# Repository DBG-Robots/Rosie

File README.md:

# Rosie

A small robot controller board for learning ROS and micro-ROS. It was designed by the DBG-Robots team at the Dietrich-Bonhoeffer-Gymnasium Oberasbach for students between 14 and 18.

**Status: v0.1, not built or tested yet.** The design passes KiCad's ERC and DRC and was checked against the datasheets, but no board has been powered up. The first batch is ordered from JLCPCB, and this README will get a "what we got wrong" section once the boards arrive. Treat everything below as the plan, not as proven.

## What it is for

We teach robotics to students who mostly have never touched a microcontroller, let alone ROS. The usual options are either a Raspberry Pi with a pile of loose modules and jumper wires, or a finished kit where you can't see how anything works.

Rosie sits in between. One board holds everything a small wheeled robot needs: the ESP32-S3, four motor outputs with encoder inputs, servo outputs, power handling, and a few connectors for sensors. The ESP32 talks to a computer running ROS 2 through micro-ROS, so students write robot code the way professionals do and never solder a motor driver.

Two decisions shaped the whole board:

1. **Nothing to wire for the standard case.** The motor connectors match the motor we use, so a student plugs in a cable and drives.
2. **Mistakes should be survivable.** A reversed battery, a stalled motor or a shorted servo cable should trip a protection instead of destroying the board, because the board will be handled by teenagers in a classroom.

## Features

- **ESP32-S3-WROOM-1-N8R2** module (8 MB flash, 2 MB PSRAM), USB-C for flashing, serial and power.
- **Four DC motor outputs** from two DRV8833 dual H-bridges. Each output has an encoder input (quadrature, ESP32 pulse counters).
- **Two servo headers** with their own current-limited supply.
- **Lidar/UART header** with 5 V, **Qwiic/I2C** socket plus an extra I2C pin header, and a **6-pin GPIO header** (J12, four free ESP32 pins named P1 to P4).
- **RGB LED** (WS2812-compatible) and a **buzzer** for status and "hello world" feedback.
- **Battery voltage measurement** so firmware can warn before the cells run flat.
- **EN and BOOT buttons**, and a **power switch**.
- **Debug LEDs and test pads** so students (and we) can see which rail or fault is the problem without a multimeter in hand.
- **Mounting holes on LEGO's 8 mm grid** (72 × 64 mm apart), so the board can be bolted to Technic frames.

## Power

Rosie runs from **four AA cells in a flat holder** fixed under the board (NiMH 1900 to 2500 mAh gives roughly three hours, alkaline cells also work). That is 4.0 to 6.4 V.

> **Rosie does not charge batteries.** There is no charger on the board. Charge NiMH cells in an external AA charger and only then put them in the holder. Do not connect anything other than 4 AA cells (max 6.4 V) to the battery connector. Do not put lithium cells there.

Why AA cells and not a LiPo: they are cheap, they can be bought in any shop, students swap them in seconds, and a classroom full of lithium cells and 14-year-olds is a risk we did not want. The price is that the voltage sags and that the board needs a good 3.3 V converter.

### Rails

| Rail | Comes from | Feeds |
|---|---|---|
| +BATT | AA holder, through a resettable fuse and a reverse-polarity P-FET | power switch |
| VSYS | after the power switch, 4.0 to 6.4 V | motors, servo supply, logic supply |
| VBUS | USB-C | logic supply only |
| VLOGIC | the higher of VSYS and VBUS (two Schottky diodes) | the 3.3 V converter |
| +3V3 | TPS62130A buck converter, 3.31 V | ESP32, pull-ups, buzzer, 5 V converter |
| +5V | TPS61023 boost converter from 3.3 V, 5.06 V | RGB LED, lidar header |
| VSERVO | TPS259571 eFuse, 2 A limit | servo headers |
| +3V3_EXT | SY6280 switch, 0.57 A limit | encoders, I2C, GPIO header |
| +5V_EXT | SY6280 switch, 0.68 A limit | lidar header |

The important consequences:

- **USB powers only the logic.** You can plug in USB to flash and debug without the motors or servos moving. Motors need the battery and the power switch.
- **USB never feeds the battery rails.** The two diodes stop current going the other way.
- **The 3.3 V converter runs from 3 to 17 V and can stay at 100 % duty**, so the ESP32 keeps running while the cells droop towards 4 V. A linear regulator would have lost the 3.3 V earlier and wasted battery as heat.
- **Servos get their own protected rail.** A shorted servo cable current-limits and shuts down that rail only. The ESP32 keeps running and the red SRV ERR LED turns on if it overheats.
- **Encoders and sensors are supplied by switches with a current limit** (SY6280), so a shorted sensor cable does not take the 3.3 V rail down with it.

## Connectors

All pinouts are listed from pin 1.

| Ref | Connector | Pins |
|---|---|---|
| J1 | USB-C | power, flashing, serial console |
| J2 | JST XH, 2-pin | battery: pin 1 = +, pin 2 = GND |
| J3 to J6 | JST ZH 1.5 mm, 6-pin | motors M1 to M4: 1 motor-, 2 GND, 3 encoder A, 4 encoder B, 5 +3.3 V, 6 motor+ |
| J7 | JST SH, 4-pin | Qwiic: GND, 3.3 V, SDA, SCL |
| J8 | 2.54 mm header, 4-pin | I2C: GND, 3.3 V, SDA, SCL |
| J9, J10 | 2.54 mm header, 3-pin | servo 1 and 2: GND, servo supply, signal |
| J11 | 2.54 mm header, 4-pin | lidar UART: GND, 5 V, RX, TX |
| J12 | 2.54 mm header, 6-pin | GND, 3.3 V, P1, P2, P3, P4 |

The motors are numbered counter-clockwise looking from above: M1 front-left, M2 rear-left, M3 rear-right, M4 front-right.

The motor connector order is that of the **CHIHAI CHF-GM12-N20** gear motor with its 6-pin ZH cable (6 V, hall encoder). Other N20 motors use other pin orders, and a wrong order can swap encoder power and ground. Plug a new motor type in with the board unpowered and check with a multimeter first.

Every encoder, servo, UART and GPIO signal passes through a 1 kΩ series resistor. A wrong connection then pushes only a milliamp or two into the ESP32 pin instead of burning it.

## Debug LEDs and test pads

| LED | Silk | Lights when |
|---|---|---|
| green | 3V3 | the 3.3 V rail is up |
| green | USB | USB power is present |
| green | BAT ON | the power switch is on and the battery is connected |
| yellow | MOT ON | firmware has enabled the motor drivers |
| red | MOT ERR | a DRV8833 reports overcurrent, overheating or undervoltage |
| red | SRV ERR | the servo eFuse shut down because of overheating |

If a rail is in doubt, the 1.5 mm round **test pads** on the top side give direct access to BAT, VSYS, VBUS, VLOG, 3V3, 5V, 3V3X, 5VX, VSRV, EN, BOOT, MOT_EN, MOT_FLT, VBAT and three ground points. Hold a multimeter probe on the pad and a second one on GND.

The four expansion pins on J12 are labelled P1 to P4 on the board on purpose. We did not want ESP32 GPIO numbers printed on the silk, because students would start thinking in pin numbers instead of functions. A student guide will map P1 to P4 to GPIOs.

## GPIO map

| GPIO | Function |
|---|---|
| IO6, IO7 | M1 PWM inputs |
| IO16, IO15 | M2 PWM inputs |
| IO37, IO38 | M3 PWM inputs |
| IO40, IO39 | M4 PWM inputs |
| IO5, IO4 | encoder 1 A, B |
| IO17, IO18 | encoder 2 A, B |
| IO36, IO35 | encoder 3 A, B |
| IO41, IO42 | encoder 4 A, B |
| IO10 | motor driver enable (internal pull-down, so motors stay off while the ESP32 boots) |
| IO21 | motor driver fault input (both drivers wired together) |
| IO8, IO9 | I2C SDA, SCL |
| IO11, IO12 | servo 1 and 2 PWM |
| IO43, IO44 | UART0 TX, RX (lidar header) |
| IO47 | buzzer |
| IO48 | RGB LED data |
| IO1, IO2, IO13, IO14 | J12 pins P1 to P4 (P1 and P2 can read analog) |
| IO3 | battery voltage (divider 1:3, so 6.4 V reads as 2.13 V) |
| IO0, IO19, IO20 | BOOT, USB D-, USB D+ |
| IO45, IO46 | strapping pins, not connected |

The firmware should **ramp the motors up** instead of jumping to full power. Four stalled N20 motors can briefly pull more than the AA cells can give, and the resulting voltage dip can reset the ESP32. Warn at 4.4 V battery voltage and stop the motors at 4.0 V.

## Design decisions

### Parts and cost

The board is built for **JLCPCB Economic assembly**, which means single-sided SMD assembly, and a limited parts catalogue. Every part was checked for stock and Economic eligibility. JLC charges $3.07 for each *unique* "Extended" part per order and nothing extra for "Basic" parts, so we:

- chose Basic parts wherever one exists (all the resistors except the 0.2 Ω shunts, all capacitors, diodes, MOSFETs, LEDs, buttons),
- recalculated the voltage dividers to values that exist as Basic resistors (3.3 V: 47 k / 15 k, 5 V: 15 k / 2 k),
- accepted 14 Extended parts, because there is no Basic alternative for the ICs, USB-C connector, ZH connector, inductor, fuse, buzzer and RGB LED.

The first order of five assembled boards came to roughly $112 before shipping and VAT, which is about $22 per board. More boards per order is the cheapest way to lower that, since the Extended-part fee is fixed.

The ESP32 module, the pin headers, the XH battery connector and the slide switch are **hand-soldered**. The JST ZH motor connectors are through-hole too, but JLC solders them. The full list with LCSC numbers is in [PARTS.md](PARTS.md), including the checks against the datasheets.

### Board and layout

- 80 × 72 mm, **four layers**: top = parts and power, inner 1 = unbroken ground, inner 2 = 3.3 V plane with a few thin power traces, bottom = signals. We chose four layers because the DRV8833s and the buck converter need a quiet ground, and because the cost difference at this size is small.
- All SMD parts are on the top side, because Economic assembly does single-sided only.
- The bottom side is flat enough that a 4×AA holder can be taped or screwed under the board. No through-hole parts sit in the 62 × 58 mm area in the middle of the bottom. Where the holder goes is up to the student; the board has no holder holes.
- The four M3 mounting holes are 72 × 64 mm apart, which is 9 × 8 studs on LEGO's 8 mm grid. Bolt them to Technic beams or use standoffs. The solder tails and the AA holder need 5 to 8 mm of room below.
- Signals were routed by hand by the team. The autorouter was tried and dropped.

### Motor drivers

The DRV8833 is a cheap, well-known dual H-bridge, with a current limit set by resistors. We use the two-pin PWM mode, and all four outputs share one enable and one fault line. Four motors on two chips keep the part count low.

### Protection

- A P-FET (not a diode) handles reverse battery polarity, so there is almost no voltage drop.
- A 3 A resettable fuse sits after the battery connector. Be aware that this kind of fuse trips at lower current when warm (about 2.3 A at 50 °C), so a warm robot can trip it at stall currents a cold one handles.
- USB data lines have an ESD protection chip.
- Servo and sensor rails have current limiting as described above.

### Silkscreen

JLCPCB wants silkscreen text at least 1.0 mm tall with a 0.15 mm stroke, so all labels are at that size or larger. The slide switch has no ON/OFF labels yet, because we have not verified which direction is ON on the real part.

The QR code at the top right links to our GitHub organization. It is drawn as silkscreen so that the code area is mask-coloured on a white silk background, which scans like a printed code.

## Files

| Path | What |
|---|---|
| `Rosie.kicad_pro`, `.kicad_sch`, `.kicad_pcb` | KiCad 10 project. Sheets: MCU, power input, power conversion, motor drivers, I/O peripherals, USB, debug |
| `libs/` | project symbols, footprints and 3D models for the parts that KiCad's own libraries do not have |
| `libs/3d-generator/` | script that generates the simplified 3D models (needs FreeCAD) |
| `production/` | Gerbers (`Rosie.zip`), JLC BOM and position files |
| `PARTS.md` | part numbers, datasheet checks, rail and GPIO tables |
| `docs/` | pictures |

Open `Rosie.kicad_pro` in KiCad 10. The library tables use relative paths, so it should work wherever you clone it.

## Known open points

- The ON direction of the slide switch SW3 is unverified (hence no labels).
- No hardware test yet. First checks when boards arrive: all red LEDs dark with only USB connected, 3.3 V and 5 V rails measured, 5 V rail noise after the divider change, LED brightness.
- 3D models are simplified and drawn from datasheet outlines, not from the manufacturers' CAD.
- Silkscreen: four footprint outlines (USB-C and the ESP32 footprint) reach past the board edge. This is harmless.

## Licence

Hardware design files (schematics, PCB, footprints, models, production files): **CERN-OHL-S-2.0**, see [LICENSE-hardware.txt](LICENSE-hardware.txt). In short: you may build, modify and sell it, but if you share a modified design, it has to stay open under the same licence. Firmware and software live in separate repositories with their own licences.

## Credits

Designed by Merlin Ortner with the DBG-Robots team, Dietrich-Bonhoeffer-Gymnasium Oberasbach.

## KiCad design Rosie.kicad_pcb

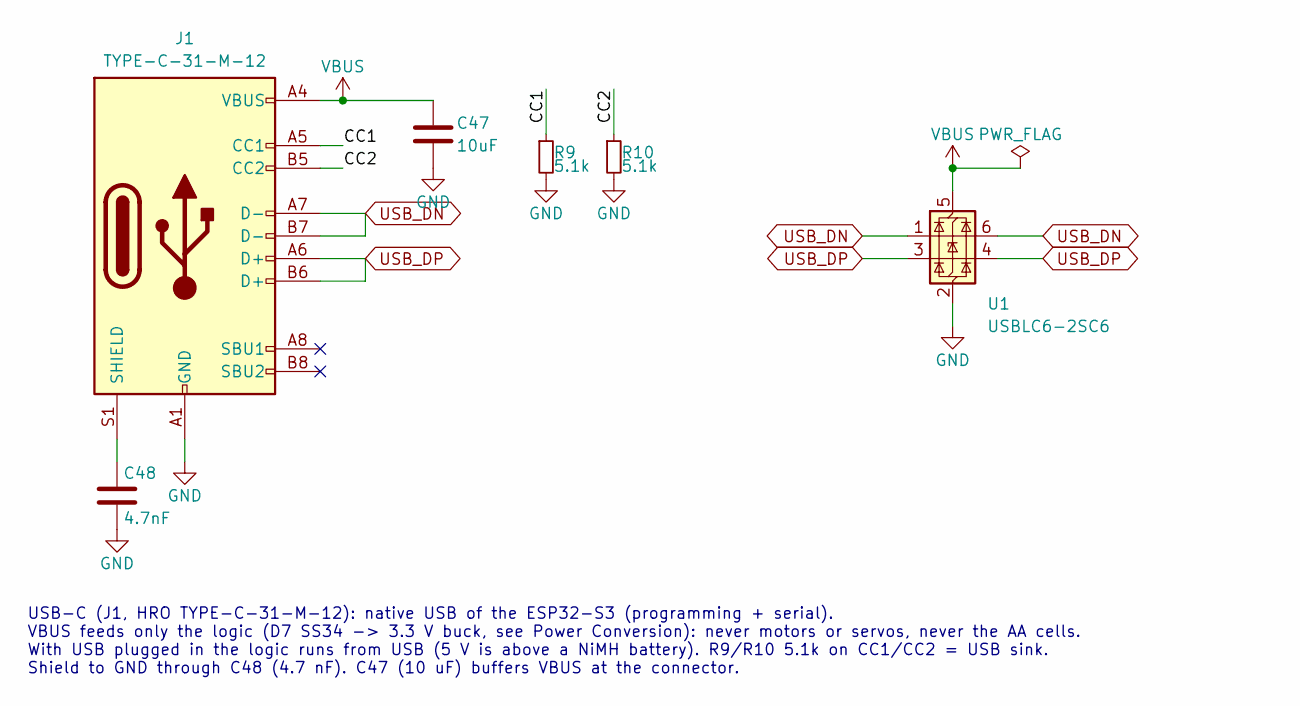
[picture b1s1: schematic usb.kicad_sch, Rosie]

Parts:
C47: 10uF; C_0805_2012Metric
C48: 4.7nF; C_0402_1005Metric
J1: TYPE-C-31-M-12; USB_C_Receptacle_HRO_TYPE-C-31-M-12; LCSC Part C165948
R9, R10: 5.1k; R_0402_1005Metric
U1: USBLC6-2SC6; SOT-23-6; LCSC Part C7519

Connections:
/USB/CC1: J1.A5 (CC1), R9.1
/USB/CC2: J1.B5 (CC2), R10.1
GND: C47.2, C48.2, J1.A1 (GND), J1.A12 (GND), J1.B1 (GND), J1.B12 (GND), R9.2, R10.2, U1.2 (GND); also elsewhere on the board
unnamed: C48.1, J1.S1 (SHIELD)
USB_DN: J1.A7 (D-), J1.B7 (D-), U1.1 (I/O1), U1.6 (I/O1); also elsewhere on the board
USB_DP: J1.A6 (D+), J1.B6 (D+), U1.3 (I/O2), U1.4 (I/O2); also elsewhere on the board
VBUS: C47.1, J1.A4 (VBUS), J1.A9 (VBUS), J1.B4 (VBUS), J1.B9 (VBUS), U1.5 (VBUS); also elsewhere on the board

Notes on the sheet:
USB-C (J1, HRO TYPE-C-31-M-12): native USB of the ESP32-S3 (programming + serial). VBUS feeds only the logic (D7 SS34 -> 3.3 V buck, see Power Conversion): never motors or servos, never the AA cells. With USB plugged in the logic runs from USB (5 V is above a NiMH battery). R9/R10 5.1k on CC1/CC2 =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

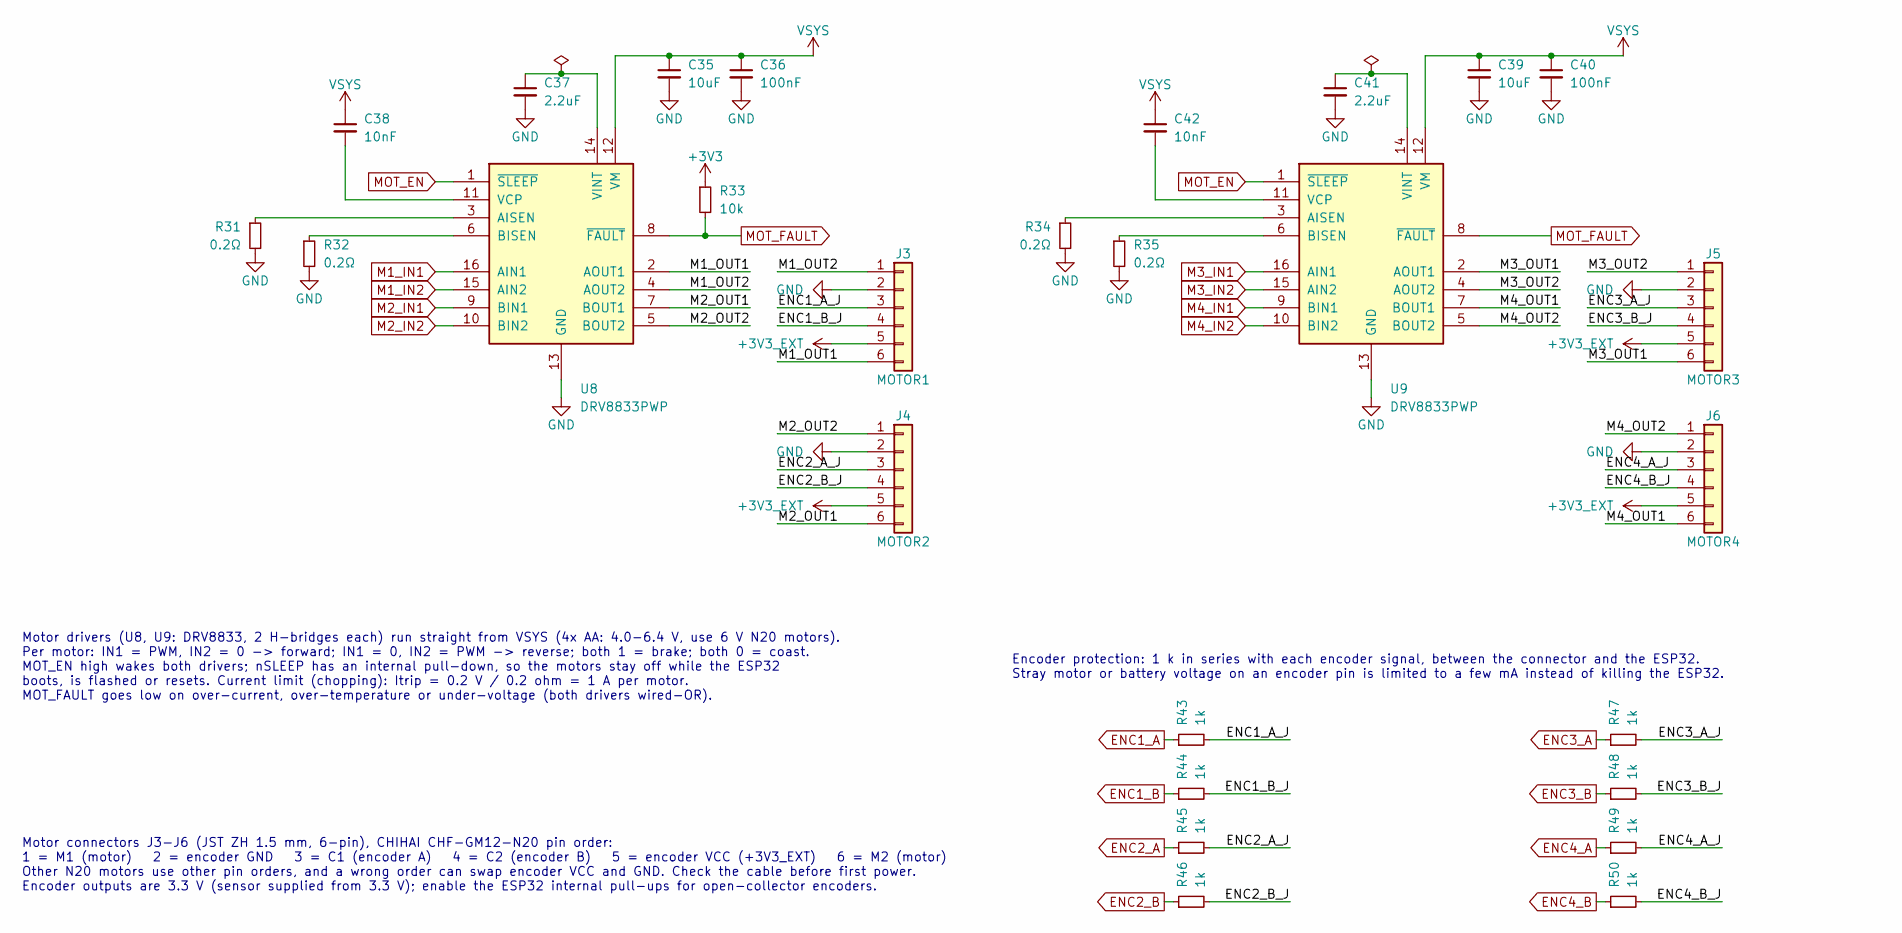
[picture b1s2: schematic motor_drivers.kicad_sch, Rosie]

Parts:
C35, C39: 10uF; C_0805_2012Metric
C36, C40: 100nF; C_0402_1005Metric
C37, C41: 2.2uF; C_0402_1005Metric
C38, C42: 10nF; C_0402_1005Metric
J3: MOTOR1; JST_ZH_B6B-ZR_1x06_P1.50mm_Vertical; LCSC Part C157984
J4: MOTOR2; JST_ZH_B6B-ZR_1x06_P1.50mm_Vertical; LCSC Part C157984
J5: MOTOR3; JST_ZH_B6B-ZR_1x06_P1.50mm_Vertical; LCSC Part C157984
J6: MOTOR4; JST_ZH_B6B-ZR_1x06_P1.50mm_Vertical; LCSC Part C157984
R31, R32, R34, R35: 0.2Ω; R_1206_3216Metric
R33: 10k; R_0402_1005Metric
R43, R44, R45, R46, R47, R48, R49, R50: 1k; R_0402_1005Metric
U8, U9: DRV8833PWP; HTSSOP-16-1EP_4.4x5mm_P0.65mm_EP3.4x5mm_ThermalVias_D0.3; LCSC Part C50506

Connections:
+3V3: R33.1; also elsewhere on the board
+3V3_EXT: J3.5, J4.5, J5.5, J6.5; also elsewhere on the board
/Motor Drivers/ENC1_A_J: J3.3, R43.2
/Motor Drivers/ENC1_B_J: J3.4, R44.2
/Motor Drivers/ENC2_A_J: J4.3, R45.2
/Motor Drivers/ENC2_B_J: J4.4, R46.2
/Motor Drivers/ENC3_A_J: J5.3, R47.2
/Motor Drivers/ENC3_B_J: J5.4, R48.2
/Motor Drivers/ENC4_A_J: J6.3, R49.2
/Motor Drivers/ENC4_B_J: J6.4, R50.2
/Motor Drivers/M1_OUT1: J3.6, U8.2 (AOUT1)
/Motor Drivers/M1_OUT2: J3.1, U8.4 (AOUT2)
/Motor Drivers/M2_OUT1: J4.6, U8.7 (BOUT1)
/Motor Drivers/M2_OUT2: J4.1, U8.5 (BOUT2)
/Motor Drivers/M3_OUT1: J5.6, U9.2 (AOUT1)
/Motor Drivers/M3_OUT2: J5.1, U9.4 (AOUT2)
/Motor Drivers/M4_OUT1: J6.6, U9.7 (BOUT1)
/Motor Drivers/M4_OUT2: J6.1, U9.5 (BOUT2)
ENC1_A: R43.1; also elsewhere on the board
ENC1_B: R44.1; also elsewhere on the board
ENC2_A: R45.1; also elsewhere on the board
ENC2_B: R46.1; also elsewhere on the board
ENC3_A: R47.1; also elsewhere on the board
ENC3_B: R48.1; also elsewhere on the board
ENC4_A: R49.1; also elsewhere on the board
ENC4_B: R50.1; also elsewhere on the board
GND: C35.2, C36.2, C37.2, C39.2, C40.2, C41.2, J3.2, J4.2, J5.2, J6.2, R31.2, R32.2, R34.2, R35.2, U8.13 (GND), U8.17 (GND), U9.13 (GND), U9.17 (GND); also elsewhere on the board
M1_IN1: U8.16 (AIN1); also elsewhere on the board
M1_IN2: U8.15 (AIN2); also elsewhere on the board
M2_IN1: U8.9 (BIN1); also elsewhere on the board
M2_IN2: U8.10 (BIN2); also elsewhere on the board
M3_IN1: U9.16 (AIN1); also elsewhere on the board
M3_IN2: U9.15 (AIN2); also elsewhere on the board
M4_IN1: U9.9 (BIN1); also elsewhere on the board
M4_IN2: U9.10 (BIN2); also elsewhere on the board
MOT_EN: U8.1 (~SLEEP), U9.1 (~SLEEP); also elsewhere on the board
MOT_FAULT: R33.2, U8.8 (~FAULT), U9.8 (~FAULT); also elsewhere on the board
unnamed: R31.1, U8.3 (AISEN)
unnamed: R32.1, U8.6 (BISEN)
unnamed: C38.2, U8.11 (VCP)
unnamed: C37.1, U8.14 (VINT)
unnamed: R34.1, U9.3 (AISEN)
unnamed: R35.1, U9.6 (BISEN)
unnamed: C42.2, U9.11 (VCP)
unnamed: C41.1, U9.14 (VINT)
VSYS: C35.1, C36.1, C38.1, C39.1, C40.1, C42.1, U8.12 (VM), U9.12 (VM); also elsewhere on the board

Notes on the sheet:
Encoder protection: 1 k in series with each encoder signal, between the connector and the ESP32. Stray motor or battery voltage on an encoder pin is limited to a few mA instead of killing the ESP32.
Motor connectors J3-J6 (JST ZH 1.5 mm, 6-pin), CHIHAI CHF-GM12-N20 pin order: 1 = M1 (motor) 2 = encoder GND 3 = C1 (encoder A) 4 = C2 (encoder B) 5 = encoder VCC (+3V3_EXT) 6 = M2 (motor) Other N20 motors use other pin orders, and a wrong order can swap encoder VCC and GND. Check the cable before 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
Motor drivers (U8, U9: DRV8833, 2 H-bridges each) run straight from VSYS (4x AA: 4.0-6.4 V, use 6 V N20 motors). Per motor: IN1 = PWM, IN2 = 0 -> forward; IN1 = 0, IN2 = PWM -> reverse; both 1 = brake; both 0 = coast. MOT_EN high wakes both drivers; nSLEEP has an internal pull-down, so the motors s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

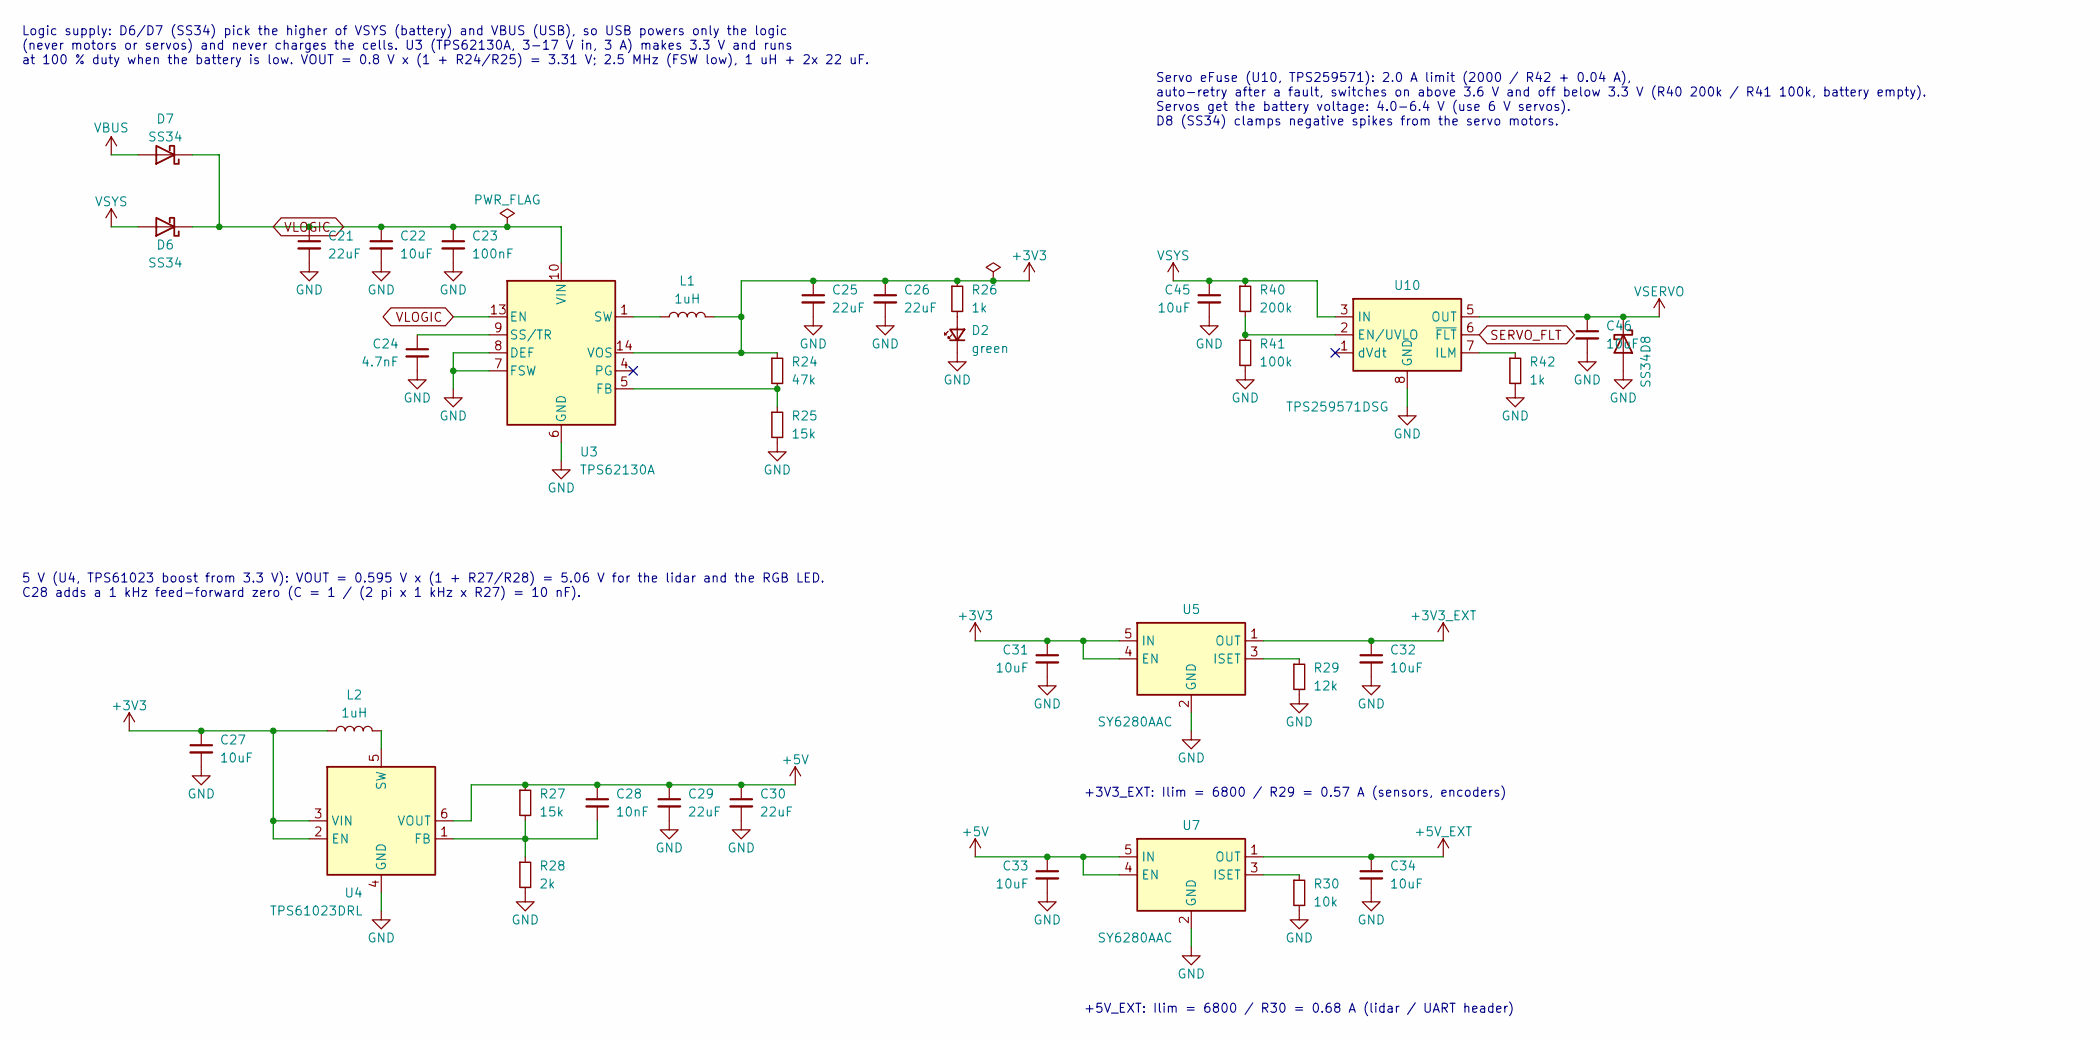
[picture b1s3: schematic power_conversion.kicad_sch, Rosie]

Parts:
C21, C25, C26, C29, C30: 22uF; C_0805_2012Metric
C22, C27, C31, C32, C33, C34, C45, C46: 10uF; C_0805_2012Metric
C23: 100nF; C_0402_1005Metric
C24: 4.7nF; C_0402_1005Metric
C28: 10nF; C_0402_1005Metric
D2: green; LED_0805_2012Metric; LCSC Part C2297
D6, D7, D8: SS34; D_SMA; LCSC Part C8678
L1, L2: 1uH; L_Changjiang_FNR4030S; LCSC Part C167865
R24: 47k; R_0402_1005Metric
R25, R27: 15k; R_0402_1005Metric
R26, R42: 1k; R_0402_1005Metric
R28: 2k; R_0402_1005Metric
R29: 12k; R_0402_1005Metric
R30: 10k; R_0402_1005Metric
R40: 200k; R_0402_1005Metric
R41: 100k; R_0402_1005Metric
U3: TPS62130A; VQFN-16-1EP_3x3mm_P0.5mm_EP1.68x1.68mm_ThermalVias_D0.3; LCSC Part C337502
U4: TPS61023DRL; SOT-563_TI_DRL; LCSC Part C919459
U5, U7: SY6280AAC; SOT-23-5; LCSC Part C55136
U10: TPS259571DSG; WSON-8-1EP_2x2mm_P0.5mm_EP0.9x1.6mm; LCSC Part C471038

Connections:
+3V3: C25.1, C26.1, C27.1, C31.1, L1.2, L2.1, R24.1, R26.1, U3.14 (VOS), U4.2 (EN), U4.3 (VIN), U5.4 (EN), U5.5 (IN); also elsewhere on the board
+3V3_EXT: C32.1, U5.1 (OUT); also elsewhere on the board
+5V: C28.1, C29.1, C30.1, C33.1, R27.1, U4.6 (VOUT), U7.4 (EN), U7.5 (IN); also elsewhere on the board
+5V_EXT: C34.1, U7.1 (OUT); also elsewhere on the board
GND: C21.2, C22.2, C23.2, C24.2, C25.2, C26.2, C27.2, C29.2, C30.2, C31.2, C32.2, C33.2, C34.2, C45.2, C46.2, D2.1 (K), D8.2 (A), R25.2, R28.2, R29.2, R30.2, R41.2, R42.2, U3.6 (GND), U3.7 (FSW), U3.8 (DEF), U3.15 (GND), U3.16 (GND), U3.17 (GND), U4.4 (GND), U5.2 (GND), U7.2 (GND), U10.8 (GND), U10.9 (GND); also elsewhere on the board
unnamed: D2.2 (A), R26.2
unnamed: L1.1, U3.1 (SW), U3.2 (SW), U3.3 (SW)
unnamed: R24.2, R25.1, U3.5 (FB)
unnamed: C24.1, U3.9 (SS/TR)
unnamed: C28.2, R27.2, R28.1, U4.1 (FB)
unnamed: L2.2, U4.5 (SW)
unnamed: R29.1, U5.3 (ISET)
unnamed: R30.1, U7.3 (ISET)
unnamed: R40.2, R41.1, U10.2 (EN/UVLO)
unnamed: R42.1, U10.7 (ILM)
SERVO_FLT: U10.6 (~FLT); also elsewhere on the board
VBUS: D7.2 (A); also elsewhere on the board
VLOGIC: C21.1, C22.1, C23.1, D6.1 (K), D7.1 (K), U3.10 (VIN), U3.11 (VIN), U3.12 (VIN), U3.13 (EN); also elsewhere on the board
VSERVO: C46.1, D8.1 (K), U10.5 (OUT); also elsewhere on the board
VSYS: C45.1, D6.2 (A), R40.1, U10.3 (IN), U10.4 (IN); also elsewhere on the board

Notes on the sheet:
5 V (U4, TPS61023 boost from 3.3 V): VOUT = 0.595 V x (1 + R27/R28) = 5.06 V for the lidar and the RGB LED. C28 adds a 1 kHz feed-forward zero (C = 1 / (2 pi x 1 kHz x R27) = 10 nF).
Logic supply: D6/D7 (SS34) pick the higher of VSYS (battery) and VBUS (USB), so USB powers only the logic (never motors or servos) and never charges the cells. U3 (TPS62130A, 3-17 V in, 3 A) makes 3.3 V and runs at 100 % duty when the battery is low. VOUT = 0.8 V x (1 + R24/R25) = 3.31 V; 2.5 MHz (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
Servo eFuse (U10, TPS259571): 2.0 A limit (2000 / R42 + 0.04 A), auto-retry after a fault, switches on above 3.6 V and off below 3.3 V (R40 200k / R41 100k, battery empty). Servos get the battery voltage: 4.0-6.4 V (use 6 V servos). D8 (SS34) clamps negative spikes from the servo motors.
+3V3_EXT: Ilim = 6800 / R29 = 0.57 A (sensors, encoders)
+5V_EXT: Ilim = 6800 / R30 = 0.68 A (lidar / UART header)

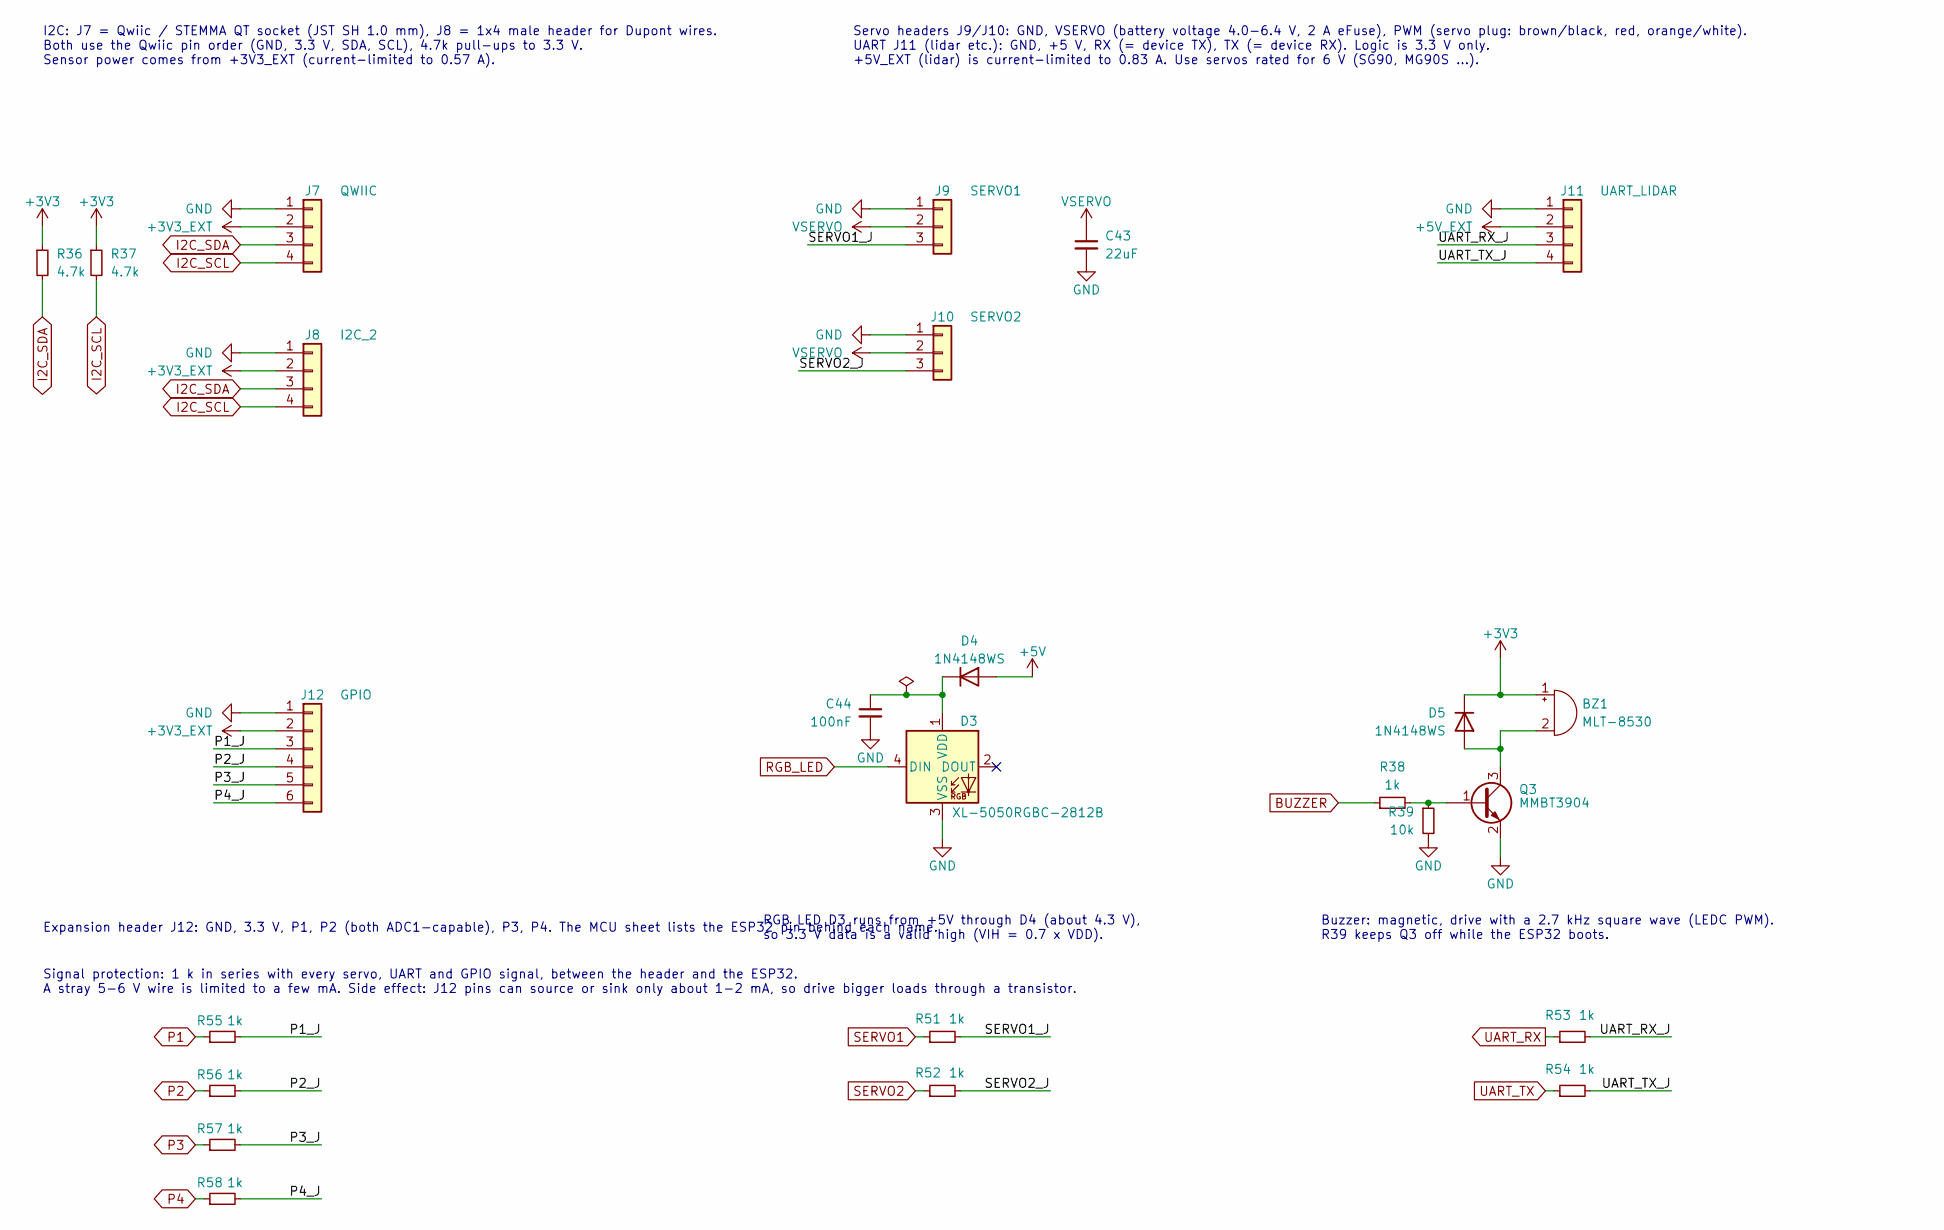
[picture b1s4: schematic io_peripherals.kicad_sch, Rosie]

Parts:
BZ1: MLT-8530; Buzzer_Huaneng_MLT-8530; LCSC Part C94599
C43: 22uF; C_0805_2012Metric
C44: 100nF; C_0402_1005Metric
D3: XL-5050RGBC-2812B; LED_WS2812B_PLCC4_5.0x5.0mm_P3.2mm; LCSC Part C48586674
D4, D5: 1N4148WS; D_SOD-323; LCSC Part C2128
J7: QWIIC; JST_SH_SM04B-SRSS-TB_1x04-1MP_P1.00mm_Horizontal; LCSC Part C160404
J8: I2C_2; PinHeader_1x04_P2.54mm_Vertical; LCSC Part C42431788 (cut to length)
J9: SERVO1; PinHeader_1x03_P2.54mm_Vertical; LCSC Part C42431788 (cut to length)
J10: SERVO2; PinHeader_1x03_P2.54mm_Vertical; LCSC Part C42431788 (cut to length)
J11: UART_LIDAR; PinHeader_1x04_P2.54mm_Vertical; LCSC Part C42431788 (cut to length)
J12: GPIO; PinHeader_1x06_P2.54mm_Vertical; LCSC Part C42431788 (cut to length)
Q3: MMBT3904; SOT-23; LCSC Part C20526
R36, R37: 4.7k; R_0402_1005Metric
R38, R51, R52, R53, R54, R55, R56, R57, R58: 1k; R_0402_1005Metric
R39: 10k; R_0402_1005Metric

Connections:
+3V3: BZ1.1 (+), D5.1 (K), R36.1, R37.1; also elsewhere on the board
+3V3_EXT: J7.2, J8.2, J12.2; also elsewhere on the board
+5V: D4.2 (A); also elsewhere on the board
+5V_EXT: J11.2; also elsewhere on the board
/IO Peripherals/P1_J: J12.3, R55.2
/IO Peripherals/P2_J: J12.4, R56.2
/IO Peripherals/P3_J: J12.5, R57.2
/IO Peripherals/P4_J: J12.6, R58.2
/IO Peripherals/SERVO1_J: J9.3, R51.2
/IO Peripherals/SERVO2_J: J10.3, R52.2
/IO Peripherals/UART_RX_J: J11.3, R53.2
/IO Peripherals/UART_TX_J: J11.4, R54.2
BUZZER: R38.1; also elsewhere on the board
GND: C43.2, C44.2, D3.3 (VSS), J7.1, J8.1, J9.1, J10.1, J11.1, J12.1, Q3.2 (E), R39.2; also elsewhere on the board
I2C_SCL: J7.4, J8.4, R37.2; also elsewhere on the board
I2C_SDA: J7.3, J8.3, R36.2; also elsewhere on the board
unnamed: BZ1.2 (-), D5.2 (A), Q3.3 (C)
unnamed: C44.1, D3.1 (VDD), D4.1 (K)
unnamed: Q3.1 (B), R38.2, R39.1
P1: R55.1; also elsewhere on the board
P2: R56.1; also elsewhere on the board
P3: R57.1; also elsewhere on the board
P4: R58.1; also elsewhere on the board
RGB_LED: D3.4 (DIN); also elsewhere on the board
SERVO1: R51.1; also elsewhere on the board
SERVO2: R52.1; also elsewhere on the board
UART_RX: R53.1; also elsewhere on the board
UART_TX: R54.1; also elsewhere on the board
VSERVO: C43.1, J9.2, J10.2; also elsewhere on the board

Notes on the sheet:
Buzzer: magnetic, drive with a 2.7 kHz square wave (LEDC PWM). R39 keeps Q3 off while the ESP32 boots.
Servo headers J9/J10: GND, VSERVO (battery voltage 4.0-6.4 V, 2 A eFuse), PWM (servo plug: brown/black, red, orange/white). UART J11 (lidar etc.): GND, +5 V, RX (= device TX), TX (= device RX). Logic is 3.3 V only. +5V_EXT (lidar) is current-limited to 0.83 A. Use servos rated for 6 V (SG90, MG90S 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
Signal protection: 1 k in series with every servo, UART and GPIO signal, between the header and the ESP32. A stray 5-6 V wire is limited to a few mA. Side effect: J12 pins can source or sink only about 1-2 mA, so drive bigger loads through a transistor.
I2C: J7 = Qwiic / STEMMA QT socket (JST SH 1.0 mm), J8 = 1x4 male header for Dupont wires. Both use the Qwiic pin order (GND, 3.3 V, SDA, SCL), 4.7k pull-ups to 3.3 V. Sensor power comes from +3V3_EXT (current-limited to 0.57 A).
RGB LED D3 runs from +5V through D4 (about 4.3 V), so 3.3 V data is a valid high (VIH = 0.7 x VDD).
Expansion header J12: GND, 3.3 V, P1, P2 (both ADC1-capable), P3, P4. The MCU sheet lists the ESP32 pin behind each name.

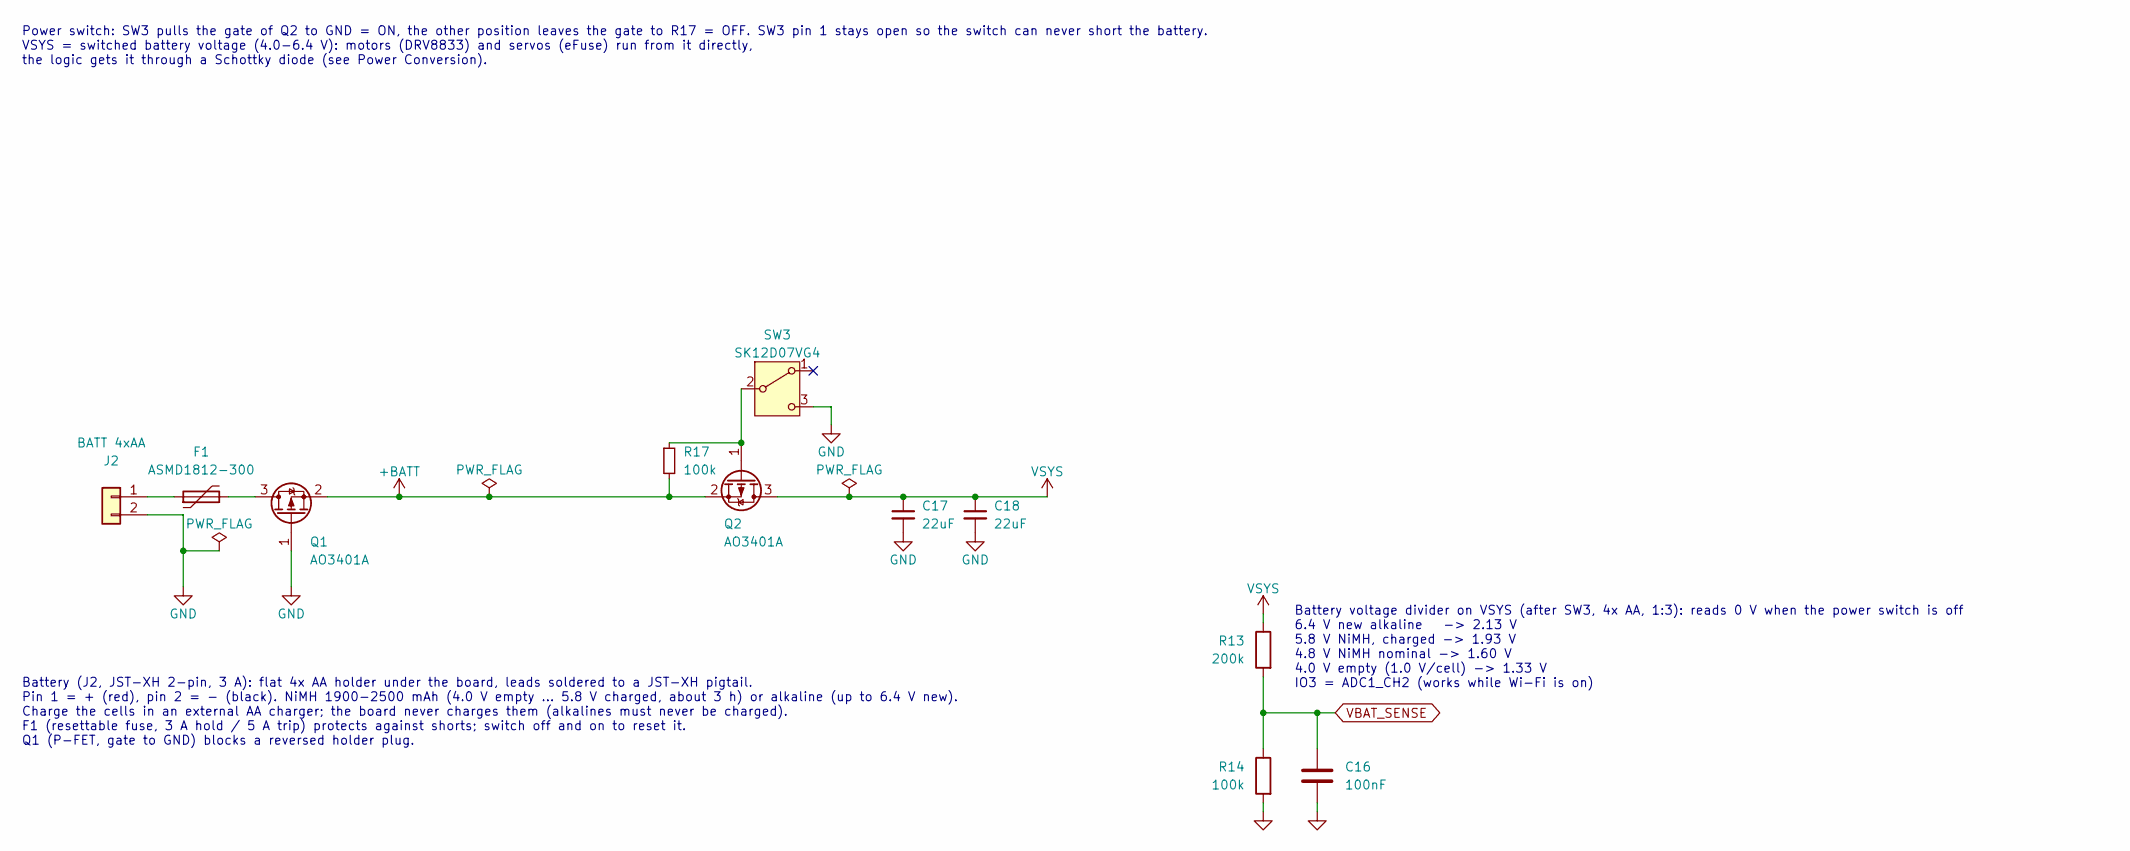
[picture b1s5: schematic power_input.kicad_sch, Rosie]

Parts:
C16: 100nF; C_0402_1005Metric
C17, C18: 22uF; C_0805_2012Metric
F1: ASMD1812-300; Fuse_1812_4532Metric; LCSC Part C135366
J2: BATT 4xAA; JST_XH_B2B-XH-A_1x02_P2.50mm_Vertical; LCSC Part C2908600
Q1, Q2: AO3401A; SOT-23; LCSC Part C15127
R13: 200k; R_0402_1005Metric
R14, R17: 100k; R_0402_1005Metric
SW3: SK12D07VG4; SW_Slide_SPDT_Angled_CK_OS102011MA1Q; LCSC Part C393937

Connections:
+BATT: Q1.2 (S), Q2.2 (S), R17.2; also elsewhere on the board
GND: C16.2, C17.2, C18.2, J2.2, Q1.1 (G), R14.2, SW3.3 (C); also elsewhere on the board
unnamed: F1.1, J2.1
unnamed: F1.2, Q1.3 (D)
unnamed: Q2.1 (G), R17.1, SW3.2 (B)
VBAT_SENSE: C16.1, R13.2, R14.1; also elsewhere on the board
VSYS: C17.1, C18.1, Q2.3 (D), R13.1; also elsewhere on the board

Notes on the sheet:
Power switch: SW3 pulls the gate of Q2 to GND = ON, the other position leaves the gate to R17 = OFF. SW3 pin 1 stays open so the switch can never short the battery. VSYS = switched battery voltage (4.0-6.4 V): motors (DRV8833) and servos (eFuse) run from it directly, the logic gets it through a Sch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
Battery voltage divider on VSYS (after SW3, 4x AA, 1:3): reads 0 V when the power switch is off 6.4 V new alkaline -> 2.13 V 5.8 V NiMH, charged -> 1.93 V 4.8 V NiMH nominal -> 1.60 V 4.0 V empty (1.0 V/cell) -> 1.33 V IO3 = ADC1_CH2 (works while Wi-Fi is on)
Battery (J2, JST-XH 2-pin, 3 A): flat 4x AA holder under the board, leads soldered to a JST-XH pigtail. Pin 1 = + (red), pin 2 = - (black). NiMH 1900-2500 mAh (4.0 V empty ... 5.8 V charged, about 3 h) or alkaline (up to 6.4 V new). Charge the cells in an external AA charger; the board never charge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

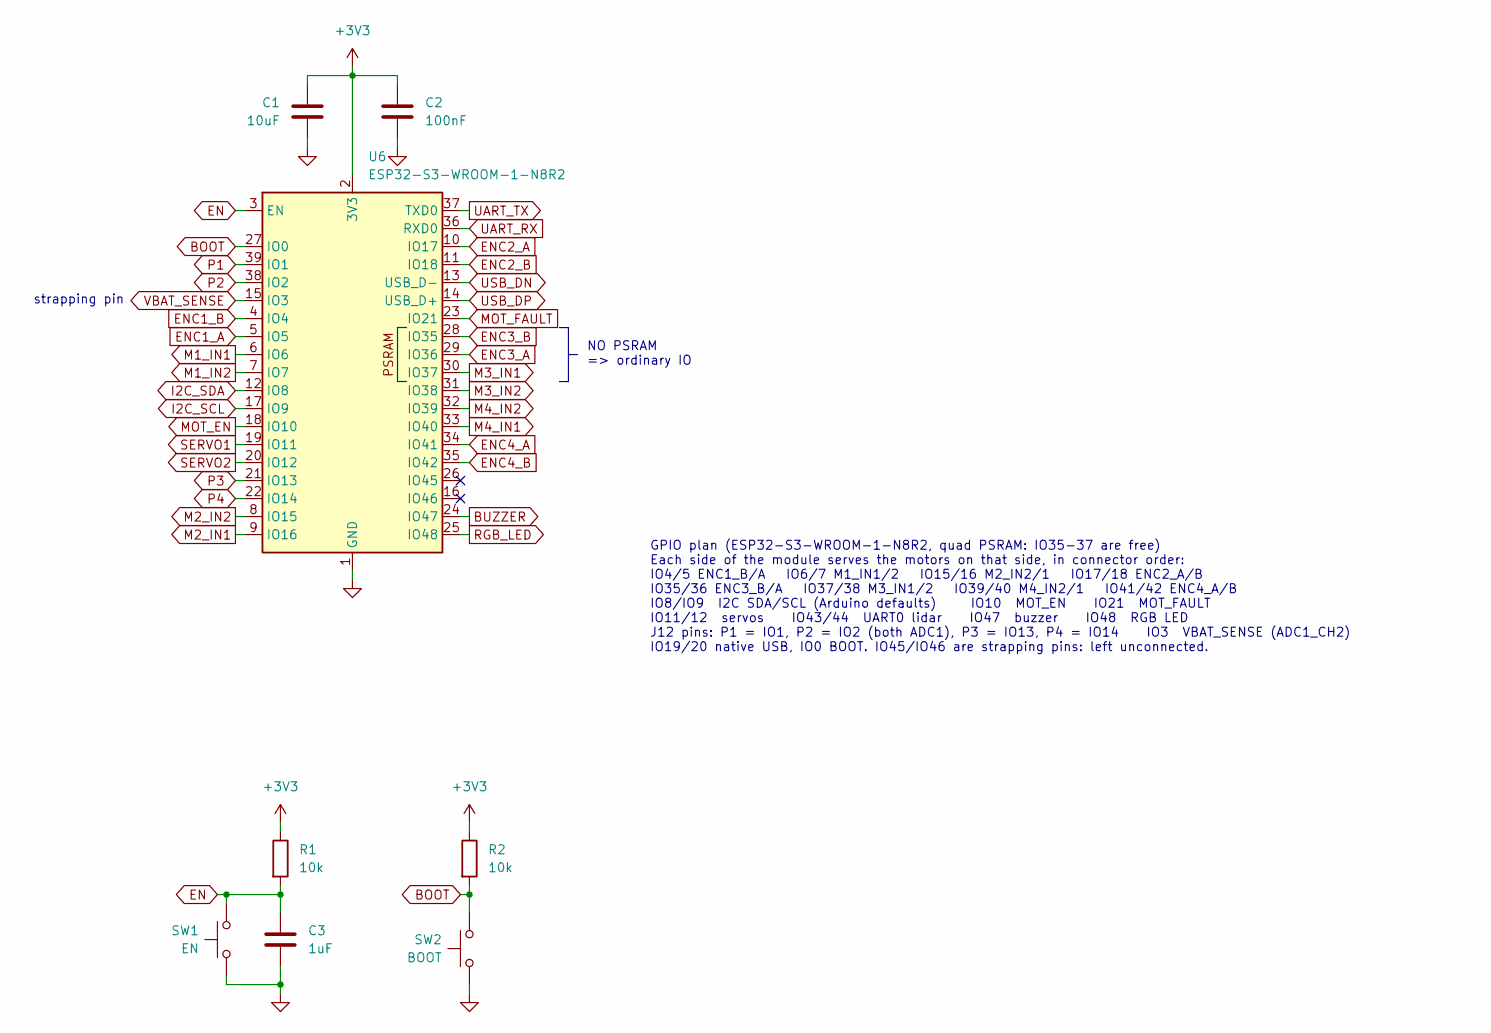
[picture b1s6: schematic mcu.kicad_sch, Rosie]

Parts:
C1: 10uF; C_0603_1608Metric
C2: 100nF; C_0402_1005Metric
C3: 1uF; C_0402_1005Metric
R1, R2: 10k; R_0402_1005Metric
SW1: EN; SW_Push_1P1T_XKB_TS-1187A; LCSC Part C318884
SW2: BOOT; SW_Push_1P1T_XKB_TS-1187A; LCSC Part C318884
U6: ESP32-S3-WROOM-1-N8R2; ESP32-S3-WROOM-1_HandSolder

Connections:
+3V3: C1.1, C2.1, R1.1, R2.1, U6.2 (3V3); also elsewhere on the board
BOOT: R2.2, SW2.2, U6.27 (IO0); also elsewhere on the board
BUZZER: U6.24 (IO47); also elsewhere on the board
EN: C3.1, R1.2, SW1.2, U6.3 (EN); also elsewhere on the board
ENC1_A: U6.5 (IO5); also elsewhere on the board
ENC1_B: U6.4 (IO4); also elsewhere on the board
ENC2_A: U6.10 (IO17); also elsewhere on the board
ENC2_B: U6.11 (IO18); also elsewhere on the board
ENC3_A: U6.29 (IO36); also elsewhere on the board
ENC3_B: U6.28 (IO35); also elsewhere on the board
ENC4_A: U6.34 (IO41); also elsewhere on the board
ENC4_B: U6.35 (IO42); also elsewhere on the board
GND: C1.2, C2.2, C3.2, SW1.1, SW2.1, U6.1 (GND), U6.40 (GND), U6.41 (GND); also elsewhere on the board
I2C_SCL: U6.17 (IO9); also elsewhere on the board
I2C_SDA: U6.12 (IO8); also elsewhere on the board
M1_IN1: U6.6 (IO6); also elsewhere on the board
M1_IN2: U6.7 (IO7); also elsewhere on the board
M2_IN1: U6.9 (IO16); also elsewhere on the board
M2_IN2: U6.8 (IO15); also elsewhere on the board
M3_IN1: U6.30 (IO37); also elsewhere on the board
M3_IN2: U6.31 (IO38); also elsewhere on the board
M4_IN1: U6.33 (IO40); also elsewhere on the board
M4_IN2: U6.32 (IO39); also elsewhere on the board
MOT_EN: U6.18 (IO10); also elsewhere on the board
MOT_FAULT: U6.23 (IO21); also elsewhere on the board
P1: U6.39 (IO1); also elsewhere on the board
P2: U6.38 (IO2); also elsewhere on the board
P3: U6.21 (IO13); also elsewhere on the board
P4: U6.22 (IO14); also elsewhere on the board
RGB_LED: U6.25 (IO48); also elsewhere on the board
SERVO1: U6.19 (IO11); also elsewhere on the board
SERVO2: U6.20 (IO12); also elsewhere on the board
UART_RX: U6.36 (RXD0); also elsewhere on the board
UART_TX: U6.37 (TXD0); also elsewhere on the board
USB_DN: U6.13 (USB_D-); also elsewhere on the board
USB_DP: U6.14 (USB_D+); also elsewhere on the board
VBAT_SENSE: U6.15 (IO3); also elsewhere on the board

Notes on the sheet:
GPIO plan (ESP32-S3-WROOM-1-N8R2, quad PSRAM: IO35-37 are free) Each side of the module serves the motors on that side, in connector order: IO4/5 ENC1_B/A IO6/7 M1_IN1/2 IO15/16 M2_IN2/1 IO17/18 ENC2_A/B IO35/36 ENC3_B/A IO37/38 M3_IN1/2 IO39/40 M4_IN2/1 IO41/42 ENC4_A/B IO8/IO9 I2C SDA/SCL (Arduin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
NO PSRAM => ordinary IO
strapping pin
